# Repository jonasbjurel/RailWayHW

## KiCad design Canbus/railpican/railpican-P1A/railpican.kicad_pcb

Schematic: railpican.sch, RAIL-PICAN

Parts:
C1: CONN_02X20; Socket_Strip_Straight_2x20
C2: 0.1uF; CP_Radial_D5.0mm_P2.00mm
C3, C8: 47uF; CP_Radial_D8.0mm_P3.50mm
C4, C5: 560pF; C_Disc_D8.0mm_W2.5mm_P5.00mm
C6, C7: 22 pF; C_Disc_D8.0mm_W2.5mm_P5.00mm
D1, D3: 1N5401; D_DO-201_P12.70mm_Horizontal
D2: GREEN; LED_D3.0mm
D4: YELLOW; LED_D3.0mm
D5: RED; LED_D3.0mm
J1: Screw_Terminal_1x04; TerminalBlock_Pheonix_MKDS1.5-4pol
J2: DB9; DB9FD
JP1: JP1; Pin_Header_Straight_1x03_Pitch2.54mm
JP2: JP2; Pin_Header_Straight_1x02_Pitch2.54mm
JP3: JP3; Pin_Header_Straight_1x03_Pitch2.54mm
JP4: JP4; Pin_Header_Straight_1x03_Pitch2.54mm
R1: 18k; R_Box_L8.4mm_W2.5mm_P5.08mm
R2, R4: 4k7; R_Box_L8.4mm_W2.5mm_P5.08mm
R3: 10k; R_Box_L8.4mm_W2.5mm_P5.08mm
R5, R8, R10: 1k; R_Box_L8.4mm_W2.5mm_P5.08mm
R6, R7: 100; R_Box_L8.4mm_W2.5mm_P5.08mm
R9: 120; R_Box_L8.4mm_W2.5mm_P5.08mm
U1: MCP2515-E/ST-DIP; DIP-18_W7.62mm
U2: 78S05; TO-220
U3: MCP2551-I/P; DIP-8_W7.62mm
Y1: Crystal; Crystal_HC49-4H_Vertical
c1: 0.1uF; CP_Radial_D5.0mm_P2.00mm

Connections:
+12V: D1.2, J1.4, J2.9
CANH: J1.3, JP2.2, JP3.2, R7.1, U3.7
CANL: J1.2, JP1.2, R6.1, R9.2, U3.6
GND: C1.6, C1.9, C1.14, C1.20, C1.30, C1.34, C1.39, C2.2, C3.2, C4.2, C5.2, C6.2, C7.2, C8.2, J1.1, JP4.2, R1.2, R4.2, R5.1, R8.1, R10.1, U1.9, U2.2, U3.2, c1.2
unnamed: C3.1, D3.2, D4.2, U2.3
unnamed: C4.1, R6.2
unnamed: C5.1, R7.2
unnamed: C8.1, D1.1, U2.1
unnamed: D2.1, R5.2
unnamed: D4.1, R8.2
unnamed: D5.1, R10.2
unnamed: J2.2, JP1.3, JP4.1
unnamed: J2.3, JP3.1, JP4.3
unnamed: J2.5, JP1.1
unnamed: J2.7, JP3.3
unnamed: JP2.1, R9.1
unnamed: R1.1, R3.2, U1.2
unnamed: R3.1, U3.4
unnamed: R4.1, U3.8
unnamed: U1.1, U3.1
OSC1: C6.1, U1.8, Y1.1
OSC2: C7.1, U1.7, Y1.2
PI_3V3: C1.1, C1.17, C2.1, R2.2, U1.18
PI_5V: C1.2, C1.4, D2.2, D3.1, U3.3, c1.1
PI_SPI_MISO: C1.21, U1.15
PI_SPI_MOSI: C1.19, U1.14
PI_SPI_SCLK: C1.23, U1.13
RST: R2.1, U1.17
~PI_SPI_CE0: C1.24, U1.16
~PI_SPI_CE1: C1.26, D5.2

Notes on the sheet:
PI connect
Power supply
Timing
CAN Activity
CANBus Logic
CAN-Interface
Control
ODBII
TERMINATION
Description
Jumper settings:
LED description:
Debug
D5 - RED: CANBUS RX/TX activity
D4 - YELLOW: +12V CANBUS Power (PI Powered by CANBUS)
D2 - GREEN: +5V PICAN HAT POWER
JP2 - CANBUS Termination: Open-No termination; Closed-R120 termination
CANBUS Termination:
CANBUS DB9 Pinout standard:
JP1:
JP3:
JP4:
(1-2)
(2-3)
2-GND; 3-CANH; 5-CANL; 9-12V+
2-CANL; 3-GND; 7-CANH; 9-12V+
DB9:
1-GND; 2-CANL; 3-CANH; 4-12V+
Screw terminal:
N/A
T.B.D.

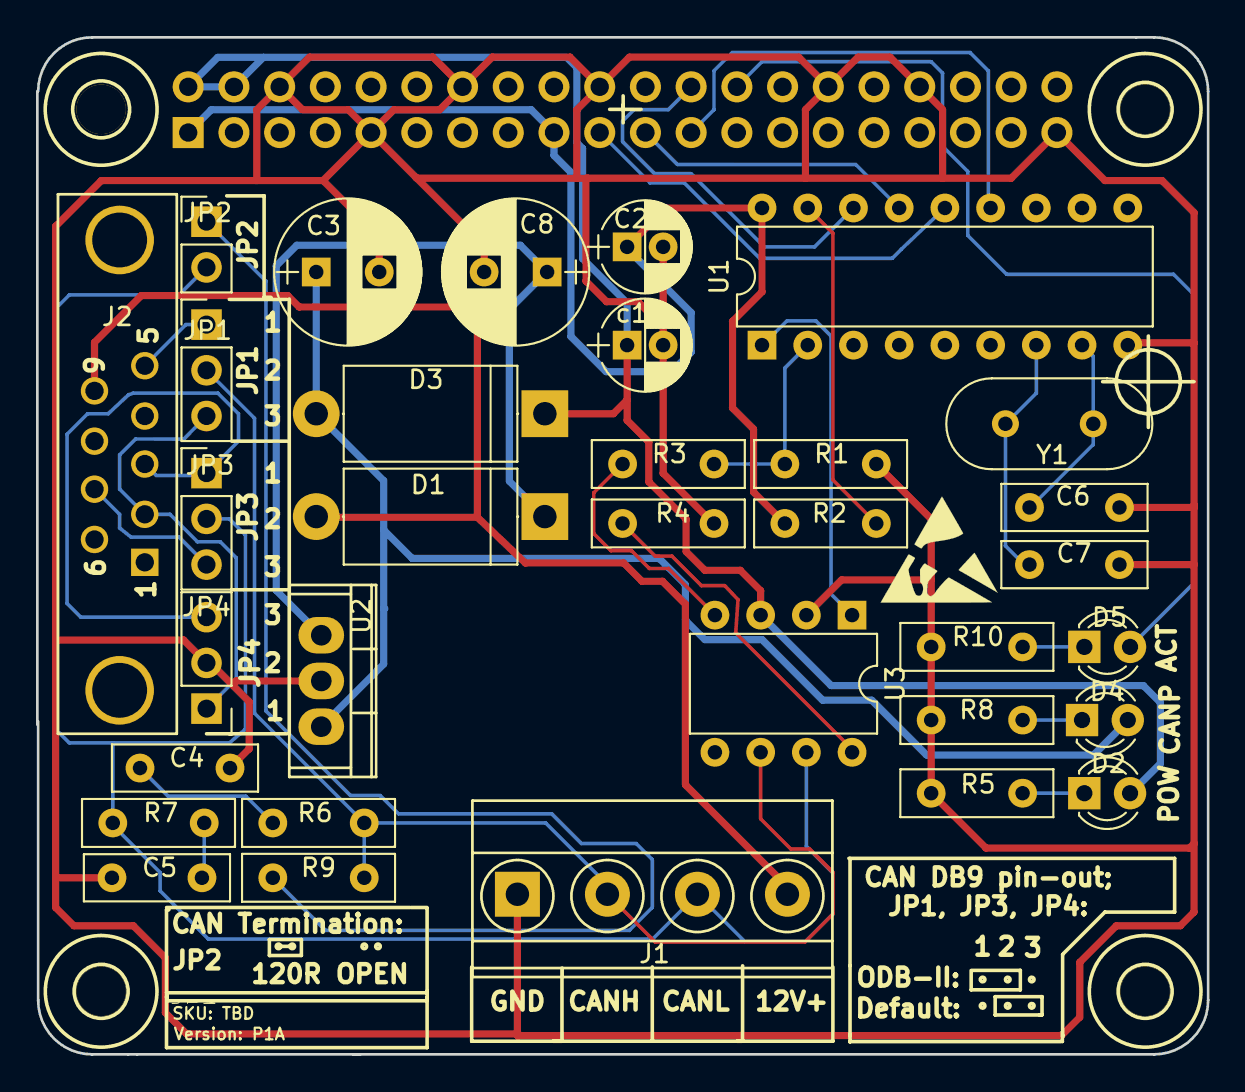
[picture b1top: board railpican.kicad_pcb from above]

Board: 2 copper layers, 65.0 x 56.5 mm, 38 parts (1 on the bottom side), 30 nets.

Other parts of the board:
H1, H2, H3, H4: DRILL; dsk-drill-rpi-hat

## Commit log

2019-11-24 Adde Erata for P1A board

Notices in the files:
Canbus/railpican/railpican-P1A/railpican.kicad_pcb:
Licence: Creative Commons (CC BY-SA 4.0)
(c) 2017 Jonas Bjurel
